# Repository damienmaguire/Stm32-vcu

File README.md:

# stm32-vcu (ZombieVerter VCU)

Project based on the OpenInverter System by Johannes Huebner to provide a universal VCU (Vehicle Control Unit) for electric vehicle conversion projects. 

Please visit the development thread on the Openinverter Forum for more information : https://openinverter.org/forum/viewtopic.php?f=3&t=1277

V1.3 Hardware now released. PDFs and Gerber here on Github, full Kicad 9 design is on Patreon at the 10Eur level.

## Required Bootloader

STM32-Serial https://github.com/jsphuebner/tumanako-inverter-fw-bootloader/releases/tag/v5.2

STM32-CAN https://github.com/jsphuebner/stm32-CANBootloader

## Videos on progress

Project introduction : https://vimeo.com/506480876

V1.11a On dyno with GS450h / BMW E39 : https://vimeo.com/802405172

V2.00a now available : https://vimeo.com/824494783?share=copy

V2.15a now available : https://www.youtube.com/watch?v=iwB3wxCEFo0

V2.20A now available : https://www.youtube.com/watch?v=wjlucUWX_lc

V2.40A now available : https://vimeo.com/1201141543?fl=ip&fe=ec

# Supported components

- Nissan Leaf Gen1/2/3 inverter via CAN
- Nissan Leaf Gen1/2/3 PDM (Charger and DCDC)
- Nissan LEAF Battery (all variants)
- Mitsubishi Outlander Support
- Mitsubishi Outlander drivetrain (front and rear motors/inverters) Support
- Modular BMS / SimpBMS Support
- OpenInverter CAN Support
- CCS DC fast charge via BMW i3 LIM
- CCS DC fast charging via FOCCCI https://github.com/uhi22/ccs32clara
- Chademo DC fast charge
- ISA Shunt / BMW SBOX / VW EBOX supported via CAN
- Lexus GS450H inverter / gearbox via sync serial
- Lexus GS300H inverter / gearbox via sync serial
- Toyota Prius/Yaris/Auris Gen 3 inverters via sync serial
- BMW E46 CAN support
- BMW E39 CAN support
- BMW E65 CAN Support
- BMW E31 CAN Support
- Mid 2000s VAG Can support
- Subaru vehicle support
- Opel Ampera / Chevy Volt 6.5kw cabin heater
- VW LIN based 6.5kw cabin heater
- Elcon charger Support
- OBD2 Can support
- TESLA Gen 2 DCDC Converter Can support

# Contributing

Information on how to contribute to this open source project can be found [Contributing Guide](./CONTRIBUTING.md)

# Compiling
You will need the arm-none-eabi toolchain: https://developer.arm.com/open-source/gnu-toolchain/gnu-rm/downloads
On Linux this can be installed by typing:

`sudo apt install gcc-arm-none-eabi`

The only external depedencies are libopencm3 and libopeninv. You can download and build this dependency by typing

`make get-deps`

Now you can compile stm32-vcu by typing

`make`

# Tests

Build the tests

`make Tests`

Run the tests

`./test/test_vcu`

And upload it to your board using a JTAG/SWD adapter, the updater.py script or the esp8266 web interface

I use CodeBlocks IDE :  https://www.codeblocks.org/

Sept 21 : V1 hardware and firmware from "Master" branch now running in my E46 Touring and E39 vehicles.

March 24 : V1.1 Hardware and V2.05A firmware now running in 3 vehicles :

-BMW E39 with Lexus GS450H Drivetrain, Tesla PCS, ISA Shunt , Chademo Fast Charge

-BMW E46 Touring with Nissan Leaf Gen 1 Drivetrain, Outlander Charger / DCDC, ISA Shunt , CCS Fast Charge

-BMW E31 with Tesla LDU Drivetrain, Tesla DCDC, ISA Shunt , Chademo Fast Charge

All hardware / software is tested in these vehicles before release. More vehicles with different configuration in progress to ensure as much testing as possible.

Apr 26 : Added Zombie Relay box V1 full kicad project to hardware directory.

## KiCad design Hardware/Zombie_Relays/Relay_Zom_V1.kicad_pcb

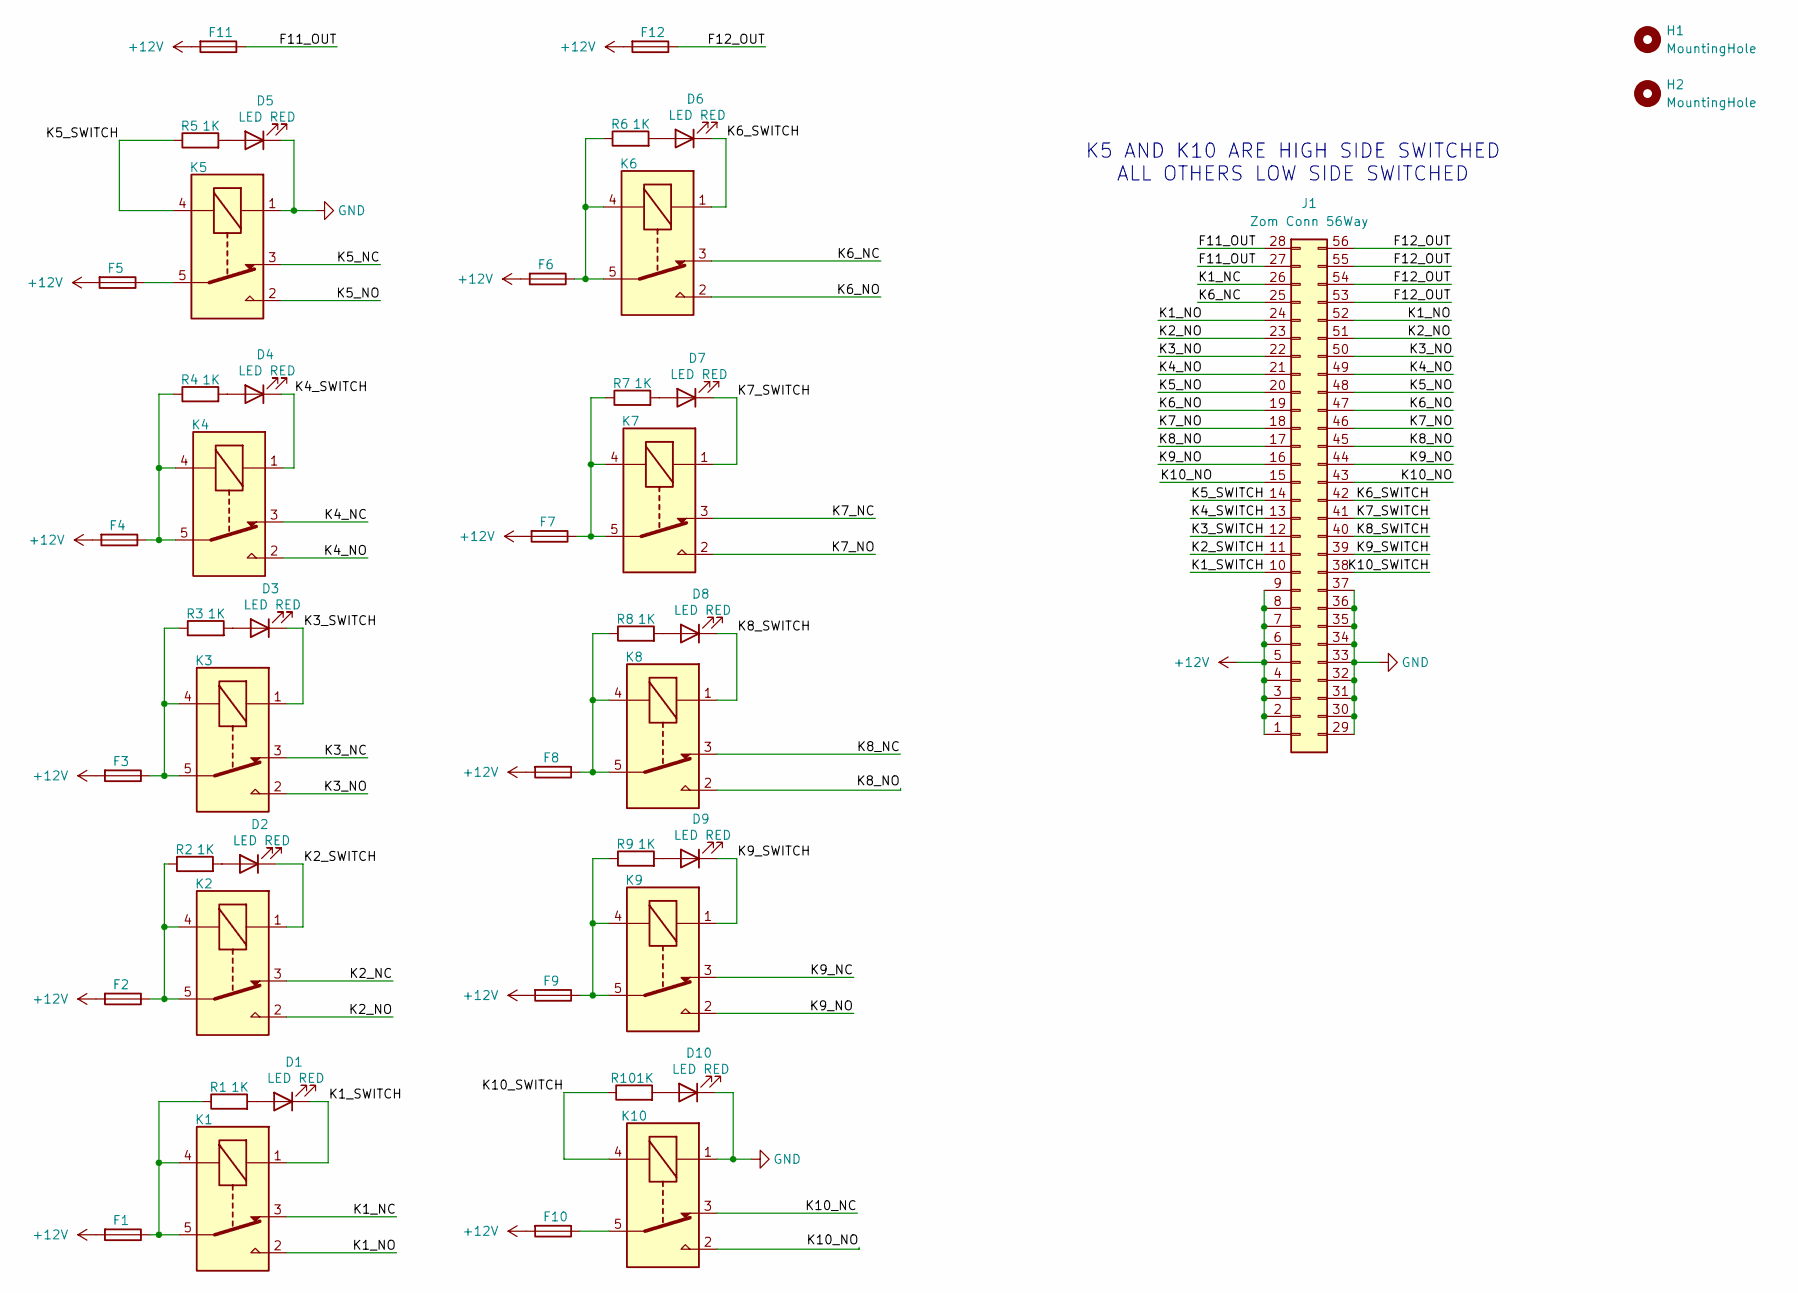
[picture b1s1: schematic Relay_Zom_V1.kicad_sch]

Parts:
D1, D2, D3, D4, D5, D6, D7, D8, D9, D10: LED RED; LED_0805_2012Metric
F1, F2, F3, F4, F5, F6, F7, F8, F9, F10, F11, F12: Fuse; 3557-2
H1, H2: MountingHole; MountingHole_4.3mm_M4
J1: Zom Conn 56Way; Header_Zom_56p
K1, K2, K3, K4, K5, K6, K7, K8, K9, K10: SRA-12VDC-CL; SRA12VDCCL; Manufacturer_Part_Number SRA-12VDC-CL
R1, R2, R3, R4, R5, R6, R7, R8, R9, R10: 1K; R_0805_2012Metric

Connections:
+12V: F1.2, F2.2, F3.2, F4.2, F5.2, F6.2, F7.2, F8.2, F9.2, F10.2, F11.2, F12.2, J1.1, J1.2, J1.3, J1.4, J1.5, J1.6, J1.7, J1.8, J1.9
/F11_OUT: F11.1, J1.27, J1.28
/F12_OUT: F12.1, J1.53, J1.54, J1.55, J1.56
/K1_NC: J1.26, K1.3
/K1_NO: J1.24, J1.52, K1.2
/K1_SWITCH: D1.1 (K), J1.10, K1.1
/K2_NC: K2.3
/K2_NO: J1.23, J1.51, K2.2
/K2_SWITCH: D2.1 (K), J1.11, K2.1
/K3_NC: K3.3
/K3_NO: J1.22, J1.50, K3.2
/K3_SWITCH: D3.1 (K), J1.12, K3.1
/K4_NC: K4.3
/K4_NO: J1.21, J1.49, K4.2
/K4_SWITCH: D4.1 (K), J1.13, K4.1
/K5_NC: K5.3
/K5_NO: J1.20, J1.48, K5.2
/K5_SWITCH: J1.14, K5.4, R5.1
/K6_NC: J1.25, K6.3
/K6_NO: J1.19, J1.47, K6.2
/K6_SWITCH: D6.1 (K), J1.42, K6.1
/K7_NC: K7.3
/K7_NO: J1.18, J1.46, K7.2
/K7_SWITCH: D7.1 (K), J1.41, K7.1
/K8_NC: K8.3
/K8_NO: J1.17, J1.45, K8.2
/K8_SWITCH: D8.1 (K), J1.40, K8.1
/K9_NC: K9.3
/K9_NO: J1.16, J1.44, K9.2
/K9_SWITCH: D9.1 (K), J1.39, K9.1
/K10_NC: K10.3
/K10_NO: J1.15, J1.43, K10.2
/K10_SWITCH: J1.38, K10.4, R10.1
GND: D5.1 (K), D10.1 (K), J1.29, J1.30, J1.31, J1.32, J1.33, J1.34, J1.35, J1.36, J1.37, K5.1, K10.1
unnamed: D1.2 (A), R1.2
unnamed: D2.2 (A), R2.2
unnamed: D3.2 (A), R3.2
unnamed: D4.2 (A), R4.2
unnamed: D5.2 (A), R5.2
unnamed: D6.2 (A), R6.2
unnamed: D7.2 (A), R7.2
unnamed: D8.2 (A), R8.2
unnamed: D9.2 (A), R9.2
unnamed: D10.2 (A), R10.2
unnamed: F1.1, K1.4, K1.5, R1.1
unnamed: F2.1, K2.4, K2.5, R2.1
unnamed: F3.1, K3.4, K3.5, R3.1
unnamed: F4.1, K4.4, K4.5, R4.1
unnamed: F5.1, K5.5
unnamed: F6.1, K6.4, K6.5, R6.1
unnamed: F7.1, K7.4, K7.5, R7.1
unnamed: F8.1, K8.4, K8.5, R8.1
unnamed: F9.1, K9.4, K9.5, R9.1
unnamed: F10.1, K10.5

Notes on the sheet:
K5 AND K10 ARE HIGH SIDE SWITCHED ALL OTHERS LOW SIDE SWITCHED

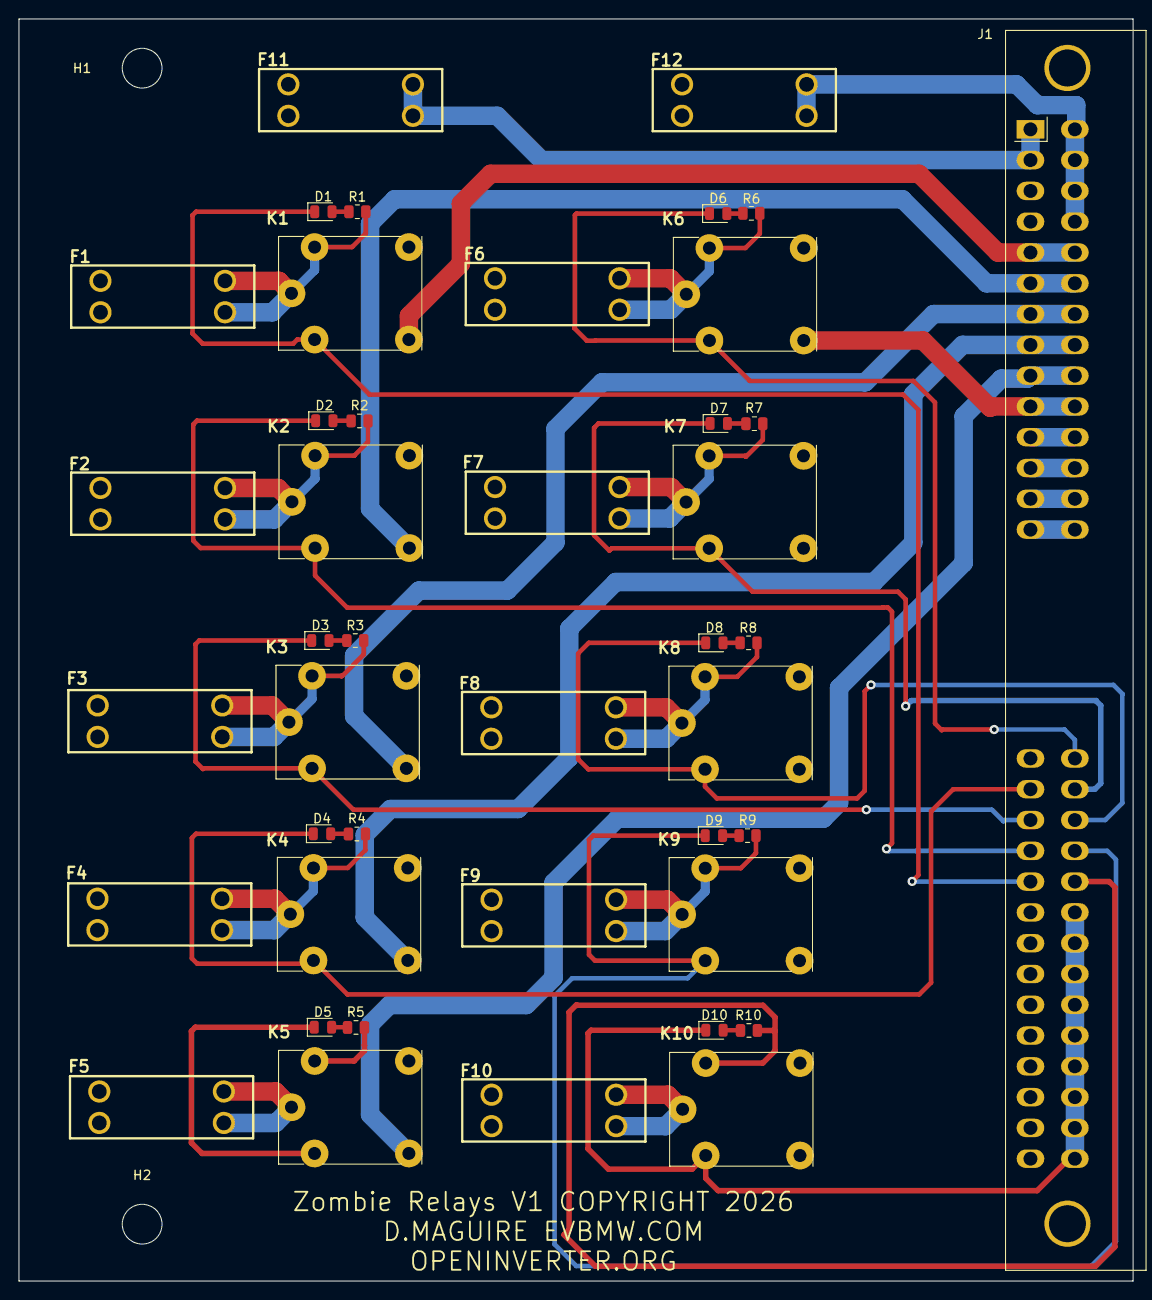
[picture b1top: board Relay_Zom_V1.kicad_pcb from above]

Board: 4 copper layers, 120.5 x 136.5 mm, 45 parts (0 on the bottom side), 46 nets.

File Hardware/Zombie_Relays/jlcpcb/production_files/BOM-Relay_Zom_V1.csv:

Comment,Designator,Footprint,LCSC,Quantity
1K,"R1,R10,R2,R3,R4,R5,R6,R7,R8,R9",R_0805_2012Metric,C17513,10
Fuse,"F1,F10,F11,F12,F2,F3,F4,F5,F6,F7,F8,F9",3557-2,C352820,12
LED RED,"D1,D10,D2,D3,D4,D5,D6,D7,D8,D9",LED_0805_2012Metric,C84256,10
SRA-12VDC-CL,"K1,K10,K2,K3,K4,K5,K6,K7,K8,K9",SRA12VDCCL,C60169,10

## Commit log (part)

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2025-02-12 SpeedoOutput option added
    Added SpeedoOutput - This is the same as TachoOutput with these changes:
    1.allows floats
    2.min speed is 200rpm
    3.only in V_Classic
    Currently only u
2025-02-12 Added PWM Output Option SOC and Temp
    -Only in Vehicle Classic
    -Min and Max duty cycle for both, can be inverted
    -Clean up PWM prescale and period
    PWM duty is - Duty x 40 = TIM_OCx
2025-02-13 Outlander update + Charger Interface Clean + HVrequest
    Interface Chademo - Does not force charge on Nissan PDM, requires PDM to report Plug Present
    Outlander Charger
    - No Charge Interface, utilize PP detect to try going into charge mode
    -will enter Charge Mode for 30s: HV ON, Inv Relay ON
    -If Charger does not report CP duty above stay in Charge Mode
    -Chademo implementation -NOT WORKING with Outlander Charger
2025-02-14 Update Makefile
2025-02-14 Update Makefile again :)
2025-02-26 ISA Shunt UDCsw
    ISA Shunt
    -Add Auto UdcSW update based on UDC2
    -Remove inspection of UDC2 and UDC3 vs UDC no longer relevant for a long time now.
2025-02-27 CAN Open Inverter Update
    CAN Control of Open Inverter board update
    1.Fix sending dir instead of hardwired inputs
    2.Auto Config of Open Inverter CAN map - Added new param to activate this
    3.include DBC for this map and OI control frame
2025-02-27 clean up
    Copy paste deletion
2025-02-28 Foccci + CANOI - CAN sleep
    Clean up of CAN sleeping and waking
    CANOI - Send CAN only when in Run Mode
    Foccci - in OFF mode on recieving PlugDetc send CAN for 1 min and wait to enter charge. If not time out
    note: Foccci should not be used with PP wake up.
2025-03-02 Add direction control to leaf command
2025-03-11 Leaf Motor Torque Limit Update
    0x1D4
    Byte 0 = Upper torque limit 2.5Nm/bit
    Byte 1 = Lower torque limit -2.5Nm/bit
    Now set to the same 617Nm. !!! Beaware of this during testing
2025-03-23 Preheat h file
2025-03-23 Fixing filename casing issue
2025-03-25 Update NissanPDM.cpp PP addition
    Also allow 0x390 byte 5 to be 0xn4 to be valid.
2025-04-04 Initial commit
    Basic DC-DC messages to test
2025-04-23 added correct DC-DC can messages
    Also added "Off" state to charger to shut down DC-DC before opening contactors
2025-04-24 dcdc fixes
    Also only sends charger shut down messages during relay delay in off mode
2025-04-24 Added V2L Messages when in run mode
2025-05-08 Correct bitshifting of Inverter voltage
2025-05-09 Create CONTRIBUTING.md
    Creating of contributing doc
2025-05-09 Options for Heater Pot
    Added more operation modes:
    1. On Off, above or below threshold
    2. Scaling above or below threshold
    Scale HeatPercent 0-100 based on threshold and full level
    Also attempt to fix MG coolant heater staying on
    Note: sacling DOES NOTHING for most heaters right now
2025-05-11 small changes to formatting
2025-05-15 Test for setting voltage and current ramp
2025-05-17 Remove throtramprpm
    throtramprpm causes major issues and will be removed until it is requested to be added back in.
2025-06-13 Update bmw_sbox.cpp
    Fix for scaling to mV
2025-06-13 BMW and VAG Sbox
    Force values to 0 in OFF opmode to make sure no erroneous precharges
2025-06-13 Revert "Merge branch 'Vehicle_Testing' into master"
    This reverts commit 923dea53bc7fe81bf60e69fc7abd39c420f83d4a, reversing
    changes made to 945fcab8d7bb1f6c053a4302622bf48196a160fb.
2025-06-14 Correction MG Gen2 Charger
    fixes to the MG Gen 2 Charger merge, no actual code changes just fixes to build
2025-06-19 Add Emus BMS integration with default extended ID address on CAN.
2025-07-08 Addition of PDK Shifter & Initial MLBEVO Charger via CAN1 or CAN2 - Also separated MagicByte Calc to a separate function for global use.
2025-07-08 Fixing filename cases
2025-07-08 Rename outlanderCompressor.h to OutlanderCompressor.h
2025-07-08 Update stm32_vcu.cpp Capitals
    Outlander is capital
2025-07-15 First commit
    Adding P1 vehicle. Only basic tests conducted so far.
2025-07-18 Update OI CAN Class
    Change OI can class to send vcu potnom as throttle value instead of raw pot values.
2025-07-19 Update CANOI
2025-07-19 Revert "tweaks"
    This reverts commit 364a0aec7382a591fa83a0421dcdc6187f307076.
2025-07-19 Revert "revert Throttle::CalcThrottle to V2.05"
    This reverts commit 39003013ef1c4e9077caf9acb7b8f611dac998ad.
2025-07-19 add speed limit back
2025-07-19 UDClim update
    finalSpnt = UDCprevspnt;
2025-07-19 comment out rampup
    remove rampup for verify
2025-07-20 Adding some more unit tests for throttle
2025-07-23 Reordering of Throttle ramping eliminating ramping of limits
    MPROVEMENT
    Issue:
    Small blip and instability noticed, not always log-able, when apply low throttle levels. Issue traced to IDC and UDC limiters.
    Fix:
    Simplification of limiters and moving the throttle ramp to last step in PotNom calculation
    Additional Change:
2025-07-23 Correction - add IDClim back in
2025-07-25 Update iomatrix.h
    changed order of noregen
2025-07-26 Remove iomatrix.h from throttle.cpp
    moved into utils.cpp
2025-08-01 Leaf HV status CAN update
2025-08-04 Added can message for Elcon chargers that need it for DCDC
2025-08-05 adjust temperature, removed off mode messages
2025-08-14 Update NissLeafMng.cpp remove reverse trq limit
2025-08-14 add udc and idc derate param
2025-08-14 Make potnom float again
2025-08-15 Fixing failing test
2025-08-15 Fixing stoopid case issue
2025-08-22 Revert "Merge pull request #194 from SomersetEV/simpbms-fix"
    This reverts commit 617241c2f6a6f88c8ad0388a3a90f1cbca16a689, reversing
    changes made to c99259c40ea87ed5a176b56e5c45ccb297a92037.
2025-08-22 Add pre-commit script
2025-08-22 Code formatting with pre-commit hook
2025-08-22 Apply pre-commit formatting to code
2025-08-22 Fix build failing due to include cstdint
2025-08-22 Add Contributing.md for project
2025-08-30 Add Enable_Analog Heater Control and PWMHeater
    Control the heater with one of the analog inputs
    Drive a PWM based heater
2025-09-04 Added heatreq to heater control
    Without this it would still pull a bit of power when the heater pot was below the cut off.
2025-09-04 Add PWMHeater
2025-09-08 Add dependabot
2025-09-09 Bump actions/checkout from 4 to 5
    Bumps [actions/checkout](https://github.com/actions/checkout) from 4 to 5.
    - [Release notes](https://github.com/actions/checkout/releases)
    - [Changelog](https://github.com/actions/checkout/blob/main/CHANGELOG.md)
    - [Commits](https://github.com/actions/checkout/compare/v4...v5)
    ---
    updated-dependencies:
2025-09-09 final fix
    sorted Iomatrix order
2025-09-14 Support std CAN SDO commands and update libopeninv
    Recent libopeninv changes allow projects to support a standard set of commands via CANopen SDO. These include fetching device serialno, loading, saving parameters and rebooting the device. The standa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
    The LIN checksum algorithm has also been fixed.
    Tests:
    - Verify load, save and default commands function
    with oic and cross-check with esp8266 web
    interface
2025-09-14 Fix VWAirHeater support
    Configuring the VWAir as a Heater type was
    selecting VWCoolant which uses a completely
    different set of LIN PIDs. This looks to be a mistake
    so allow the vwAirHeater class to be configured.
    Fix a compiler error reported by gcc 15.1 in the
    include guard in VWAirHeater.h.
2025-09-14 Inverter voltage and motor temperature fix
2025-09-14 Fix version formatting
    The automated code format changes broke the
    formatting of the "version" spot value. The "units"
    field of a parameter must not contain spaces
    otherwise esp8266-web-interface, esp32-web-
    interface and OpenInverter CAN Tool will not be able
    to correctly parse it into an enum.
2025-09-15 Fix linker warning on main() with gcc 15.1
    gcc 15.1 reports:
    src/stm32_vcu.cpp:1396:16: warning: cannot declare '::main' with a linkage specification [-Wpedantic]
    Remove the unnecessary extern "C" linkage
    declaration.
    Tests:
    - Verified the binaries of a clean rebuild is identical
2025-09-15 Update MCU clock initialisation to remove warning
    Use the up to date main MCU clock initialisation code
    as used by stm32-sine and ccs32clara. There should
    be no functional change.
    This removes:
    src/hwinit.cpp:45:18: warning: 'void rcc_clock_setup_in_hse_8mhz_out_72mhz()'
    Tests:
2025-09-15 Tesla Charger Formatting clean up
2025-09-15 add more spaces teslaCharger.cpp
2025-09-15 indenting fixes teslacharger.cpp
2025-09-15 Teslacharger.cpp variable clean up
2025-09-20 Chademo and PP compatibility Update
    -PP detect is bypassed if DCFCrequest input is active
    -Chademo clean up on reading input to stop always high if un specified
    -din_cruise reused for HVreq input
2025-09-20 hvreq update
2025-11-08 Fix ipace shifter bug
2025-11-10 MG Gen1 Chg skeleton
2025-11-10 Precharge bugfix
    Fix precharge bug and confirm mg gen1 charger skeleton works
2025-11-11 MG Gen1 Charger
    Working
2025-12-23 GS450h Serial Sync Update Jamie + Throttle Float Change
    Source : https://github.com/jamiejones85/Stm32-vcu/tree/12Maintain
    GS450h- reworking sync serial for all 3 variants to run interupt based comms. Also contains auto resets
2025-12-24 Function Alignment
    -SOC PWM Output
    -Temp PWM Output
    -Speedometer Update
    -Analogue input for Heater Power
2026-01-05 Forced Format Update
2026-01-05 Fix Linbus reference error
2026-01-15 CAN OI update Header and Param update
2026-01-19 Comment out htm_data initialization for Prius
    Comment out the loop that initializes htm_data from htm_data_Prius for Gen 3 Prius inverter.
2026-01-19 format prius comment out
2026-03-02 Bump actions/upload-artifact from 6 to 7
    Bumps [actions/upload-artifact](https://github.com/actions/upload-artifact) from 6 to 7.
    - [Release notes](https://github.com/actions/upload-artifact/releases)
    - [Commits](https://github.com/actions/upload-artifact/compare/v6...v7)
    ---
    updated-dependencies:
    - dependency-name: actions/upload-artifact
2026-03-06 availableChargePower sign fix
2026-03-12 Add PR template for Github
2026-03-27 Change byte value from 0x70 to 0x07
    Reverted byte value for gen1 issues to ensure proper regeneration.
2026-03-27 Fix comment formatting in NissLeafMng.cpp
2026-03-27 remove files that will not be released
2026-03-31 Removed sending messages code
2026-04-03 Break Pin Functions in Input and Output
2026-04-03 Correct Param_prj
2026-04-03 precharge added back in
2026-04-11 Added support for Webasto HVH series
2026-04-14 Added support for AC Propulsion drive train
2026-04-20 Merge pull request #2 from jsphuebner/copilot/investigate-ci-action-failure
    Apply clang-format to AC Propulsion inverter files
2026-04-20 Add Brogen CAN map file
2026-04-21 Add 12V battery maintainer feature
    This feature allows the VCU to automatically wake up and run in maintainer
    mode to charge the 12V battery when it drops below a configured threshold.
    Changes:
    - Add Maintainer12V class for managing 12V battery maintenance
    - Add MOD_MAINTAIN operation mode
    - Add parameters: uauxGain, minVolts, allowWakeup, wakeupMin
2026-04-24 First creating
2026-04-29 Add V1.3 Hardware
2026-05-08 Intro Relative Current Control
    Int16_t changed everywhere to Int32_t for speed
    Swapped inverter and motor temp
2026-05-10 Wire iX4_Lever into the shifter selection switch
    - include/param_prj.h: add BMWiX4 = 5 to ShifterModes enum
    - src/stm32_vcu.cpp: include header, instantiate iX4GearLever,
    add the new case to UpdateShifter()
    - test/test_list.h + test/Makefile: register the unit test
2026-05-12 Fix gear lever direction not forwarded to OI inverter
    Can_OI::SetTorque() was reading din_forward/din_reverse directly,
    which are only set by physical digital inputs. When a CAN gear lever
    (F30, E65, JLR, etc.) is used, direction is resolved by SelectDirection()
    into Param::dir instead. Switch to reading Param::dir (1=forward, -1=reverse)
    so the OI inverter receives the correct direction bits regardless of
    whether a physical or CAN-based gear lever is fitted.
2026-06-21 Update libopeninv to latest upstream (jsphuebner 51a9e58)
    Bump the libopeninv submodule to current jsphuebner tip (51a9e58 — adds
    Baud100 / 33.3k, the SDO refactor, and the Send-overload fix) and adapt
    the VCU:
    - CanSdo: drop the GetPendingUserspaceSdo() main-loop poll. The new
    libopeninv ProcessSDO routes user-space SDO objects (serial 0x5000 /
    command 0x5002) to SdoCommands from HandleRx, so plain CanSdo suffices.
2026-06-27 Basic Leaf AC Control

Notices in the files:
Hardware/Zombie_Relays/Relay_Zom_V1.kicad_pcb:
Zombie Relays V1 COPYRIGHT 2026
